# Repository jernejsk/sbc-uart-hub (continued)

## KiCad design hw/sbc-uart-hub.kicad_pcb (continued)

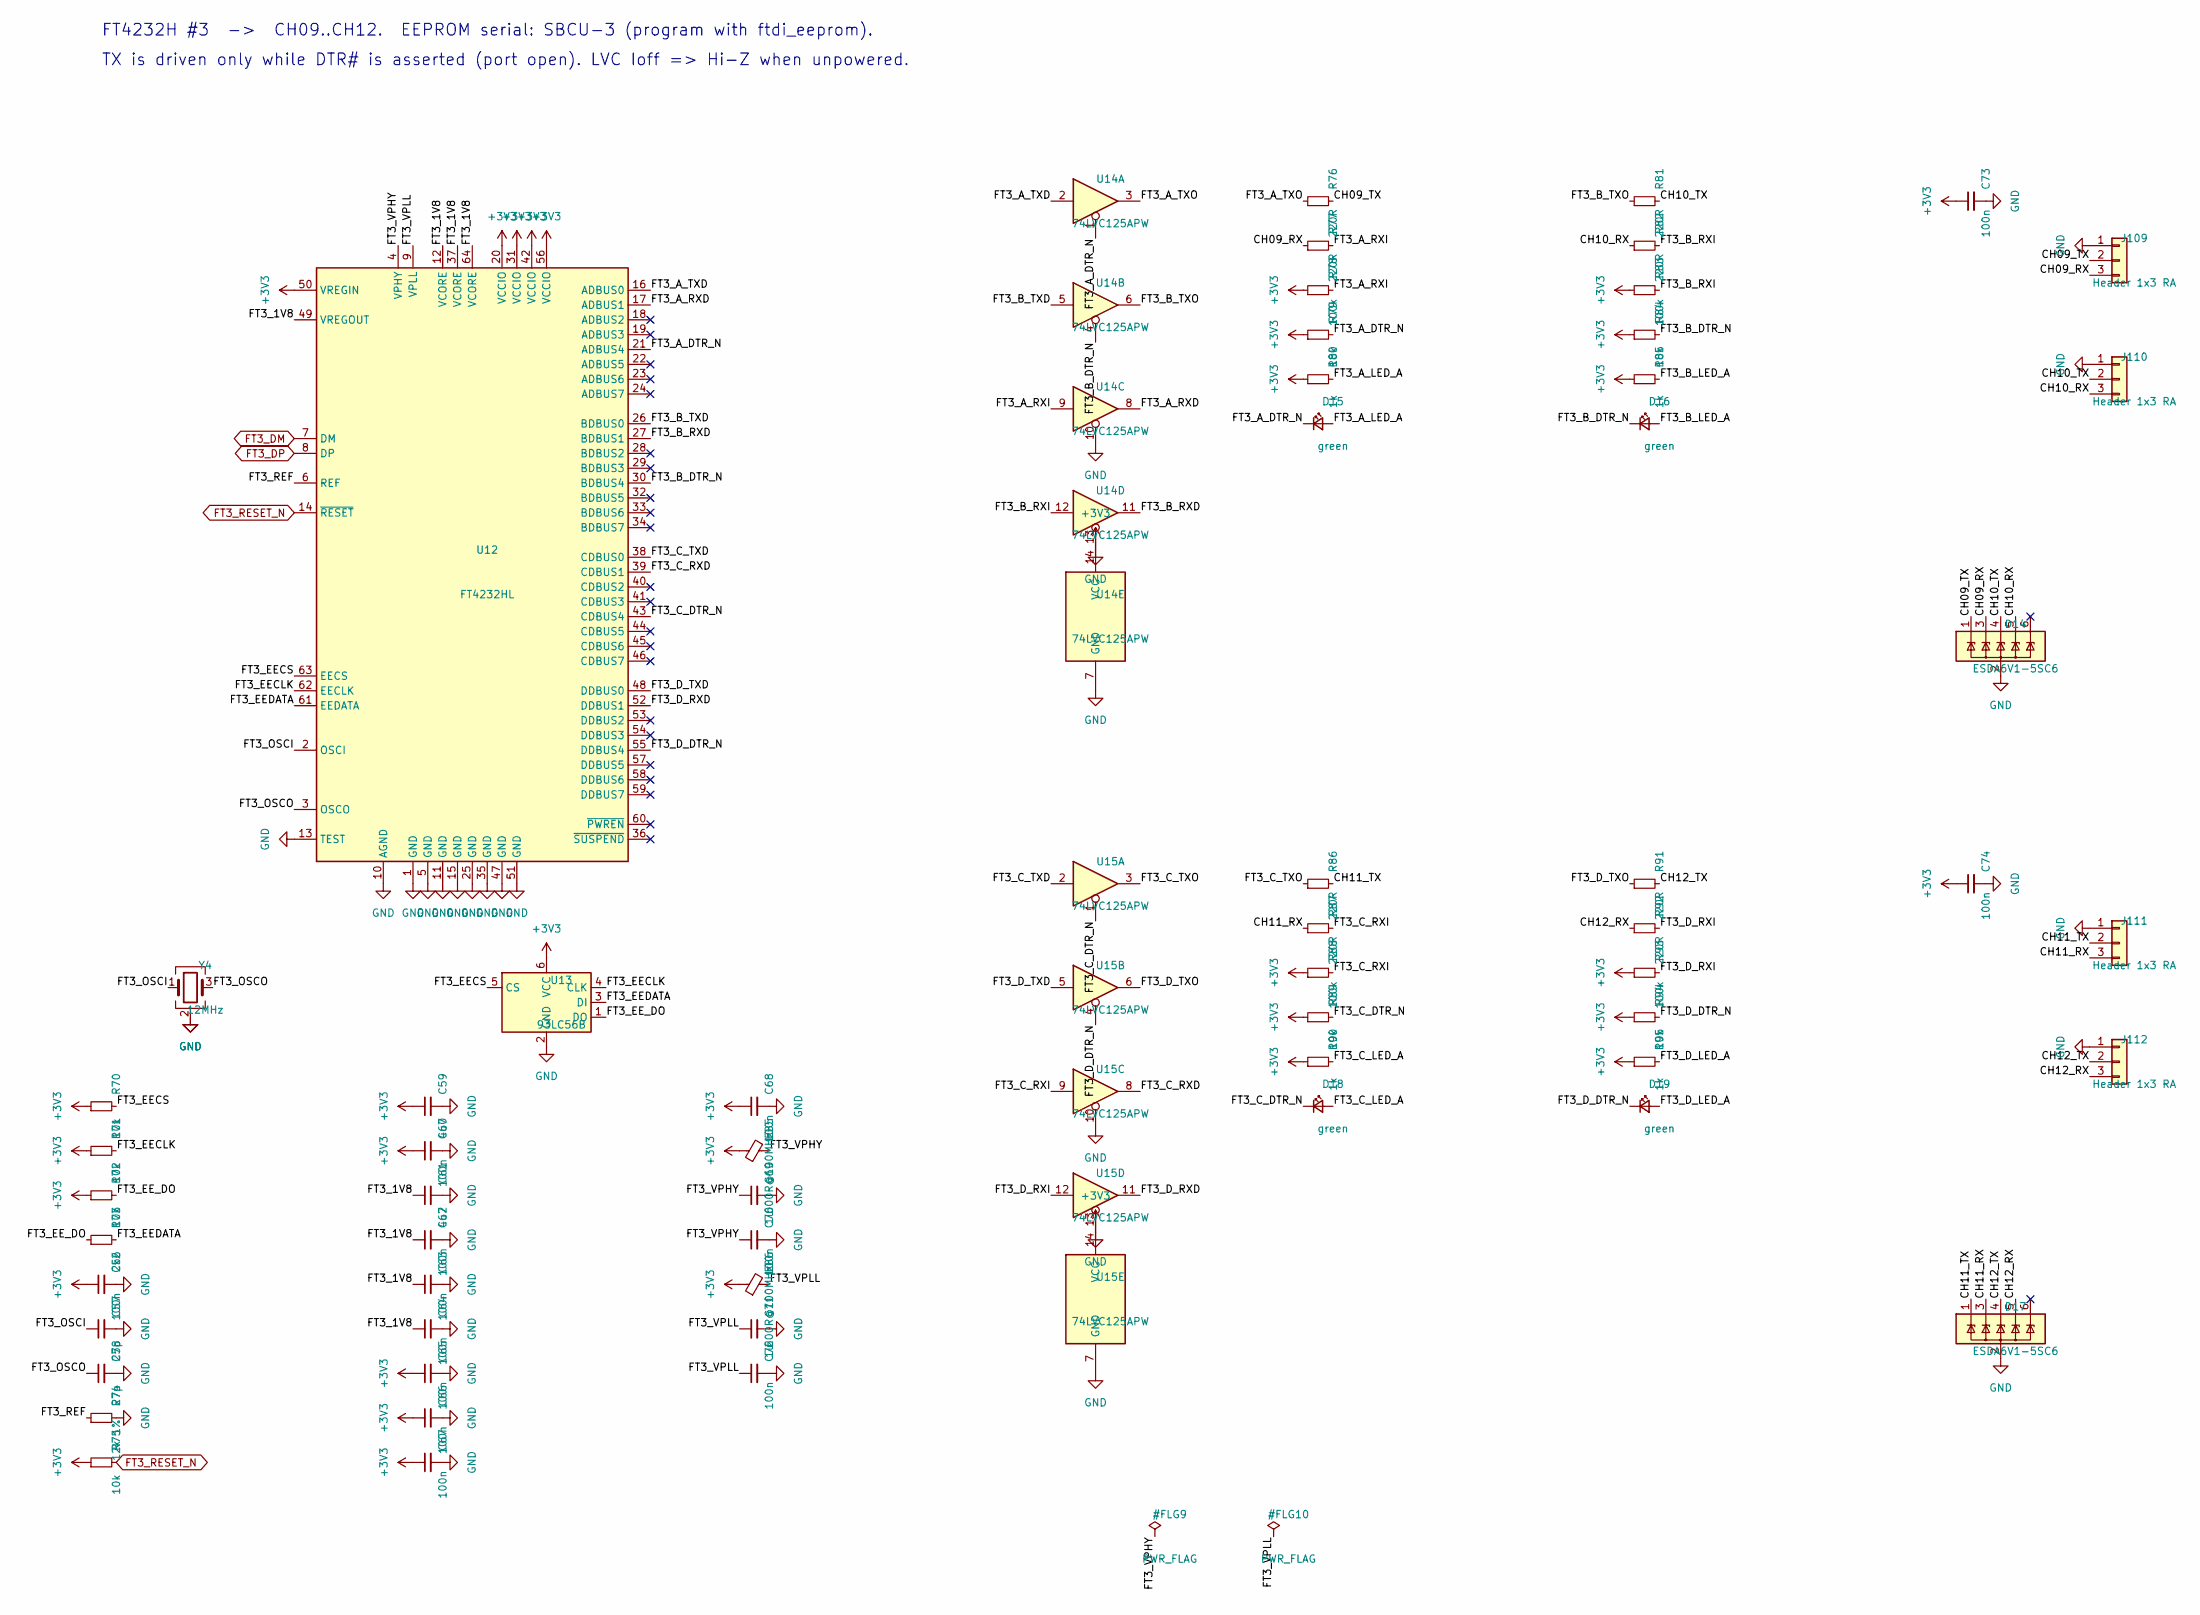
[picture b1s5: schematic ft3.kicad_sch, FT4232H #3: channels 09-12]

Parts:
C56, C60, C62, C63, C64, C65, C66, C67, C68, C70, C72, C73, C74: 100n; C_0402_1005Metric; MPN CL05B104KO5NNNC; LCSC C1525
C57, C58: 27p; C_0402_1005Metric; MPN 0402CG270J500NT; LCSC C1557
C59, C61: 4u7; C_0805_2012Metric; MPN CL21A475KAQNNNE; LCSC C1779
C69, C71: 1u; C_0402_1005Metric; MPN CL05A105KA5NQNC; LCSC C52923
D14, D17: ESDA6V1-5SC6; SOT-23-6; MPN ESDA6V1-5SC6; LCSC C2827672
D15, D16, D18, D19: green; LED_0603_1608Metric; MPN KT-0603G; LCSC C12624
FB5, FB6: 600R@100MHz; L_0603_1608Metric; MPN GZ1608D601TF; LCSC C1002
J109, J110, J111, J112: Header 1x3 RA; PinHeader_1x03_P2.54mm_Horizontal_Edge; MPN PZ254R-11-03P; LCSC C492411
R70, R71, R72, R75, R79, R84, R89, R94: 10k; R_0402_1005Metric; MPN 0402WGF1002TCE; LCSC C25744
R73: 2k2; R_0402_1005Metric; MPN 0402WGF2201TCE; LCSC C25879
R74: 12k 1%; R_0402_1005Metric; MPN 0402WGF1202TCE; LCSC C25752
R76, R77, R81, R82, R86, R87, R91, R92: 220R; R_0402_1005Metric; MPN 0402WGF2200TCE; LCSC C25091
R78, R83, R88, R93: 100k; R_0402_1005Metric; MPN 0402WGF1003TCE; LCSC C25741
R80, R85, R90, R95: 1k; R_0402_1005Metric; MPN 0402WGF1001TCE; LCSC C11702
U12: FT4232HL; LQFP-64_10x10mm_P0.5mm; MPN FT4232HL-REEL; LCSC C56742
U13: 93LC56B; SOT-23-6; MPN 93LC56BT-I/OT; LCSC C190271
U14, U15: 74LVC125APW; TSSOP-14_4.4x5mm_P0.65mm; MPN 74LVC125APW,118; LCSC C6059
Y4: 12MHz; Crystal_SMD_3225-4Pin_3.2x2.5mm; MPN X322512MSB4SI; LCSC C9002

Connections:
+3V3: C56.1, C59.1, C60.1, C65.1, C66.1, C67.1, C68.1, C73.1, C74.1, FB5.1, FB6.1, R70.1, R71.1, R72.1, R75.1, R78.1, R79.1, R80.1, R83.1, R84.1, R85.1, R88.1, R89.1, R90.1, R93.1, R94.1, R95.1, U12.20 (VCCIO), U12.31 (VCCIO), U12.42 (VCCIO), U12.50 (VREGIN), U12.56 (VCCIO), U13.6 (VCC), U14.14 (VCC), U15.14 (VCC); also elsewhere on the board
/FT3/CH09_RX: D14.3 (IO2), J109.3, R77.1
/FT3/CH09_TX: D14.1 (IO1), J109.2, R76.2
/FT3/CH10_RX: D14.5 (IO4), J110.3, R82.1
/FT3/CH10_TX: D14.4 (IO3), J110.2, R81.2
/FT3/CH11_RX: D17.3 (IO2), J111.3, R87.1
/FT3/CH11_TX: D17.1 (IO1), J111.2, R86.2
/FT3/CH12_RX: D17.5 (IO4), J112.3, R92.1
/FT3/CH12_TX: D17.4 (IO3), J112.2, R91.2
/FT3/FT3_1V8: C61.1, C62.1, C63.1, C64.1, U12.12 (VCORE), U12.37 (VCORE), U12.49 (VREGOUT), U12.64 (VCORE)
/FT3/FT3_A_DTR_N: D15.1 (K), R79.2, U12.21 (ADBUS4), U14.1
/FT3/FT3_A_LED_A: D15.2 (A), R80.2
/FT3/FT3_A_RXD: U12.17 (ADBUS1), U14.8
/FT3/FT3_A_RXI: R77.2, R78.2, U14.9
/FT3/FT3_A_TXD: U12.16 (ADBUS0), U14.2
/FT3/FT3_A_TXO: R76.1, U14.3
/FT3/FT3_B_DTR_N: D16.1 (K), R84.2, U12.30 (BDBUS4), U14.4
/FT3/FT3_B_LED_A: D16.2 (A), R85.2
/FT3/FT3_B_RXD: U12.27 (BDBUS1), U14.11
/FT3/FT3_B_RXI: R82.2, R83.2, U14.12
/FT3/FT3_B_TXD: U12.26 (BDBUS0), U14.5
/FT3/FT3_B_TXO: R81.1, U14.6
/FT3/FT3_C_DTR_N: D18.1 (K), R89.2, U12.43 (CDBUS4), U15.1
/FT3/FT3_C_LED_A: D18.2 (A), R90.2
/FT3/FT3_C_RXD: U12.39 (CDBUS1), U15.8
/FT3/FT3_C_RXI: R87.2, R88.2, U15.9
/FT3/FT3_C_TXD: U12.38 (CDBUS0), U15.2
/FT3/FT3_C_TXO: R86.1, U15.3
/FT3/FT3_D_DTR_N: D19.1 (K), R94.2, U12.55 (DDBUS4), U15.4
/FT3/FT3_D_LED_A: D19.2 (A), R95.2
/FT3/FT3_D_RXD: U12.52 (DDBUS1), U15.11
/FT3/FT3_D_RXI: R92.2, R93.2, U15.12
/FT3/FT3_D_TXD: U12.48 (DDBUS0), U15.5
/FT3/FT3_D_TXO: R91.1, U15.6
/FT3/FT3_EECLK: R71.2, U12.62 (EECLK), U13.4 (CLK)
/FT3/FT3_EECS: R70.2, U12.63 (EECS), U13.5 (CS)
/FT3/FT3_EEDATA: R73.2, U12.61 (EEDATA), U13.3 (DI)
/FT3/FT3_EE_DO: R72.2, R73.1, U13.1 (DO)
/FT3/FT3_OSCI: C57.1, U12.2 (OSCI), Y4.1
/FT3/FT3_OSCO: C58.1, U12.3 (OSCO), Y4.3
/FT3/FT3_REF: R74.1, U12.6 (REF)
/FT3/FT3_VPHY: C69.1, C70.1, FB5.2, U12.4 (VPHY)
/FT3/FT3_VPLL: C71.1, C72.1, FB6.2, U12.9 (VPLL)
FT3_DM: U12.7 (DM); also elsewhere on the board
FT3_DP: U12.8 (DP); also elsewhere on the board
FT3_RESET_N: R75.2, U12.14 (~RESET); also elsewhere on the board
GND: C56.2, C57.2, C58.2, C59.2, C60.2, C61.2, C62.2, C63.2, C64.2, C65.2, C66.2, C67.2, C68.2, C69.2, C70.2, C71.2, C72.2, C73.2, C74.2, D14.2 (GND), D17.2 (GND), J109.1, J110.1, J111.1, J112.1, R74.2, U12.1 (GND), U12.5 (GND), U12.10 (AGND), U12.11 (GND), U12.13 (TEST), U12.15 (GND), U12.25 (GND), U12.35 (GND), U12.47 (GND), U12.51 (GND), U13.2 (GND), U14.7 (GND), U14.10, U14.13, U15.7 (GND), U15.10, U15.13, Y4.2 (G), Y4.4 (G); also elsewhere on the board

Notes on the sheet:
FT4232H #3 -> CH09..CH12. EEPROM serial: SBCU-3 (program with ftdi_eeprom).
TX is driven only while DTR# is asserted (port open). LVC Ioff => Hi-Z when unpowered.

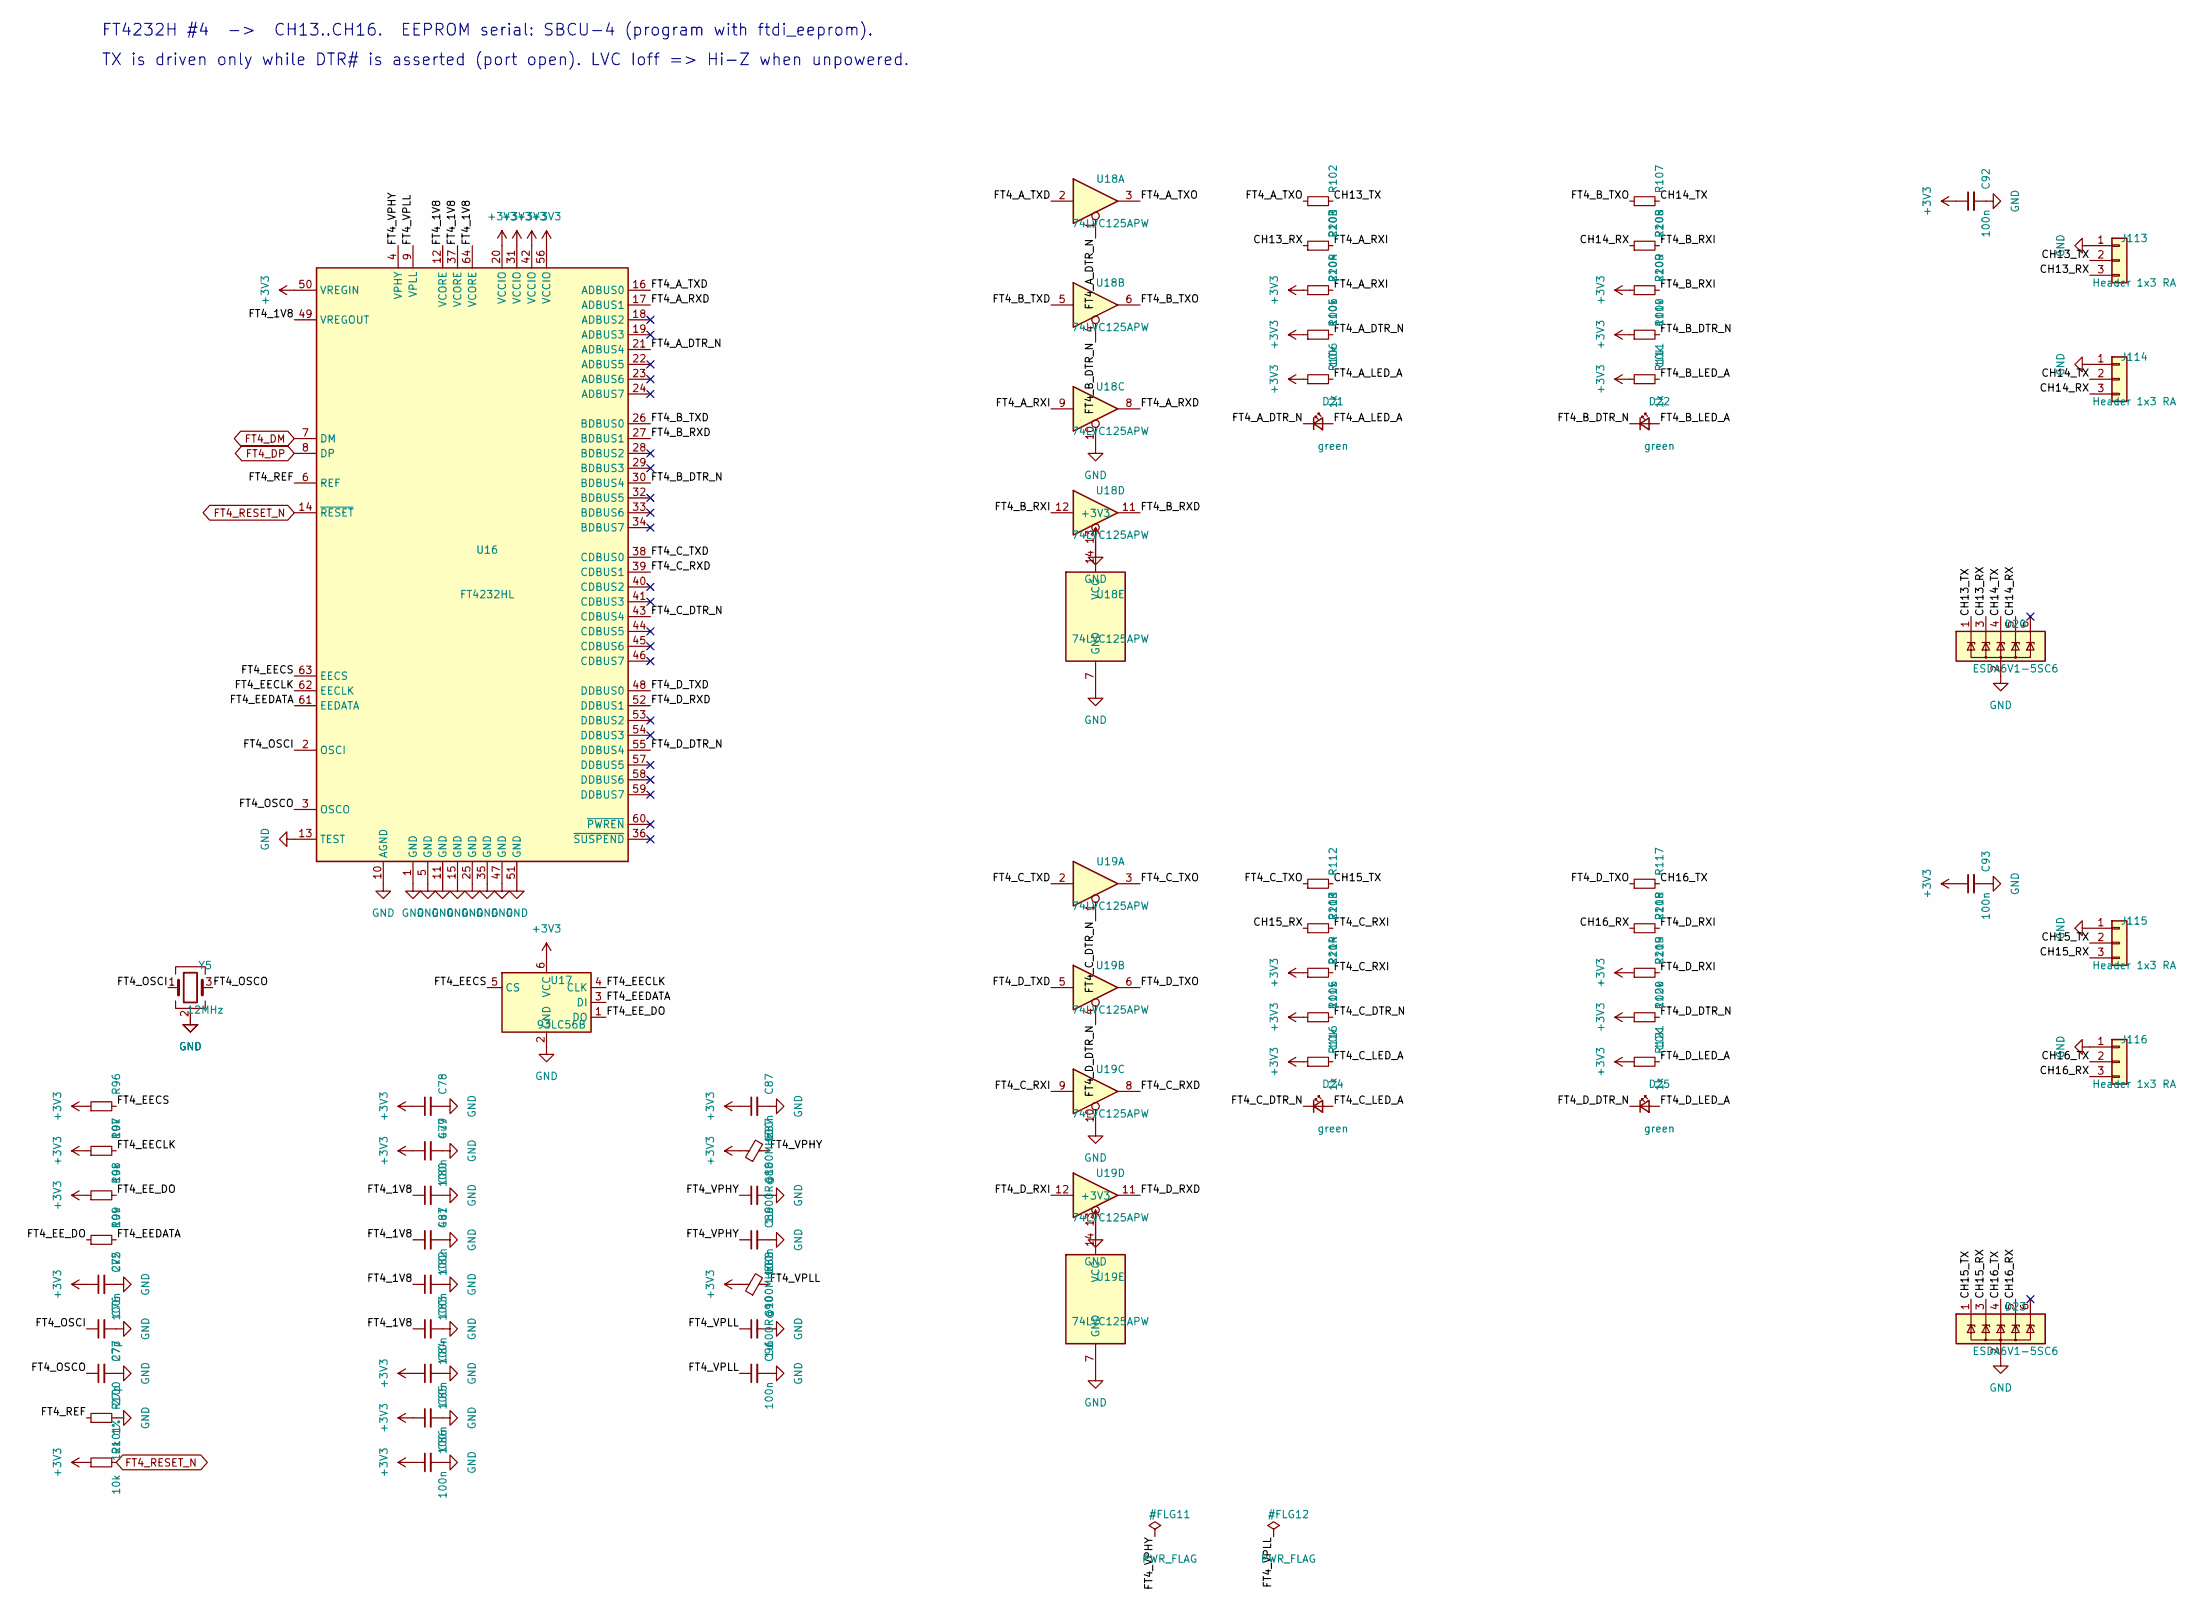
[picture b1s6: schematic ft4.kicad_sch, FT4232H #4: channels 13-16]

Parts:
C75, C79, C81, C82, C83, C84, C85, C86, C87, C89, C91, C92, C93: 100n; C_0402_1005Metric; MPN CL05B104KO5NNNC; LCSC C1525
C76, C77: 27p; C_0402_1005Metric; MPN 0402CG270J500NT; LCSC C1557
C78, C80: 4u7; C_0805_2012Metric; MPN CL21A475KAQNNNE; LCSC C1779
C88, C90: 1u; C_0402_1005Metric; MPN CL05A105KA5NQNC; LCSC C52923
D20, D23: ESDA6V1-5SC6; SOT-23-6; MPN ESDA6V1-5SC6; LCSC C2827672
D21, D22, D24, D25: green; LED_0603_1608Metric; MPN KT-0603G; LCSC C12624
FB7, FB8: 600R@100MHz; L_0603_1608Metric; MPN GZ1608D601TF; LCSC C1002
J113, J114, J115, J116: Header 1x3 RA; PinHeader_1x03_P2.54mm_Horizontal_Edge; MPN PZ254R-11-03P; LCSC C492411
R96, R97, R98, R101, R105, R110, R115, R120: 10k; R_0402_1005Metric; MPN 0402WGF1002TCE; LCSC C25744
R99: 2k2; R_0402_1005Metric; MPN 0402WGF2201TCE; LCSC C25879
R100: 12k 1%; R_0402_1005Metric; MPN 0402WGF1202TCE; LCSC C25752
R102, R103, R107, R108, R112, R113, R117, R118: 220R; R_0402_1005Metric; MPN 0402WGF2200TCE; LCSC C25091
R104, R109, R114, R119: 100k; R_0402_1005Metric; MPN 0402WGF1003TCE; LCSC C25741
R106, R111, R116, R121: 1k; R_0402_1005Metric; MPN 0402WGF1001TCE; LCSC C11702
U16: FT4232HL; LQFP-64_10x10mm_P0.5mm; MPN FT4232HL-REEL; LCSC C56742
U17: 93LC56B; SOT-23-6; MPN 93LC56BT-I/OT; LCSC C190271
U18, U19: 74LVC125APW; TSSOP-14_4.4x5mm_P0.65mm; MPN 74LVC125APW,118; LCSC C6059
Y5: 12MHz; Crystal_SMD_3225-4Pin_3.2x2.5mm; MPN X322512MSB4SI; LCSC C9002

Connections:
+3V3: C75.1, C78.1, C79.1, C84.1, C85.1, C86.1, C87.1, C92.1, C93.1, FB7.1, FB8.1, R96.1, R97.1, R98.1, R101.1, R104.1, R105.1, R106.1, R109.1, R110.1, R111.1, R114.1, R115.1, R116.1, R119.1, R120.1, R121.1, U16.20 (VCCIO), U16.31 (VCCIO), U16.42 (VCCIO), U16.50 (VREGIN), U16.56 (VCCIO), U17.6 (VCC), U18.14 (VCC), U19.14 (VCC); also elsewhere on the board
/FT4/CH13_RX: D20.3 (IO2), J113.3, R103.1
/FT4/CH13_TX: D20.1 (IO1), J113.2, R102.2
/FT4/CH14_RX: D20.5 (IO4), J114.3, R108.1
/FT4/CH14_TX: D20.4 (IO3), J114.2, R107.2
/FT4/CH15_RX: D23.3 (IO2), J115.3, R113.1
/FT4/CH15_TX: D23.1 (IO1), J115.2, R112.2
/FT4/CH16_RX: D23.5 (IO4), J116.3, R118.1
/FT4/CH16_TX: D23.4 (IO3), J116.2, R117.2
/FT4/FT4_1V8: C80.1, C81.1, C82.1, C83.1, U16.12 (VCORE), U16.37 (VCORE), U16.49 (VREGOUT), U16.64 (VCORE)
/FT4/FT4_A_DTR_N: D21.1 (K), R105.2, U16.21 (ADBUS4), U18.1
/FT4/FT4_A_LED_A: D21.2 (A), R106.2
/FT4/FT4_A_RXD: U16.17 (ADBUS1), U18.8
/FT4/FT4_A_RXI: R103.2, R104.2, U18.9
/FT4/FT4_A_TXD: U16.16 (ADBUS0), U18.2
/FT4/FT4_A_TXO: R102.1, U18.3
/FT4/FT4_B_DTR_N: D22.1 (K), R110.2, U16.30 (BDBUS4), U18.4
/FT4/FT4_B_LED_A: D22.2 (A), R111.2
/FT4/FT4_B_RXD: U16.27 (BDBUS1), U18.11
/FT4/FT4_B_RXI: R108.2, R109.2, U18.12
/FT4/FT4_B_TXD: U16.26 (BDBUS0), U18.5
/FT4/FT4_B_TXO: R107.1, U18.6
/FT4/FT4_C_DTR_N: D24.1 (K), R115.2, U16.43 (CDBUS4), U19.1
/FT4/FT4_C_LED_A: D24.2 (A), R116.2
/FT4/FT4_C_RXD: U16.39 (CDBUS1), U19.8
/FT4/FT4_C_RXI: R113.2, R114.2, U19.9
/FT4/FT4_C_TXD: U16.38 (CDBUS0), U19.2
/FT4/FT4_C_TXO: R112.1, U19.3
/FT4/FT4_D_DTR_N: D25.1 (K), R120.2, U16.55 (DDBUS4), U19.4
/FT4/FT4_D_LED_A: D25.2 (A), R121.2
/FT4/FT4_D_RXD: U16.52 (DDBUS1), U19.11
/FT4/FT4_D_RXI: R118.2, R119.2, U19.12
/FT4/FT4_D_TXD: U16.48 (DDBUS0), U19.5
/FT4/FT4_D_TXO: R117.1, U19.6
/FT4/FT4_EECLK: R97.2, U16.62 (EECLK), U17.4 (CLK)
/FT4/FT4_EECS: R96.2, U16.63 (EECS), U17.5 (CS)
/FT4/FT4_EEDATA: R99.2, U16.61 (EEDATA), U17.3 (DI)
/FT4/FT4_EE_DO: R98.2, R99.1, U17.1 (DO)
/FT4/FT4_OSCI: C76.1, U16.2 (OSCI), Y5.1
/FT4/FT4_OSCO: C77.1, U16.3 (OSCO), Y5.3
/FT4/FT4_REF: R100.1, U16.6 (REF)
/FT4/FT4_VPHY: C88.1, C89.1, FB7.2, U16.4 (VPHY)
/FT4/FT4_VPLL: C90.1, C91.1, FB8.2, U16.9 (VPLL)
FT4_DM: U16.7 (DM); also elsewhere on the board
FT4_DP: U16.8 (DP); also elsewhere on the board
FT4_RESET_N: R101.2, U16.14 (~RESET); also elsewhere on the board
GND: C75.2, C76.2, C77.2, C78.2, C79.2, C80.2, C81.2, C82.2, C83.2, C84.2, C85.2, C86.2, C87.2, C88.2, C89.2, C90.2, C91.2, C92.2, C93.2, D20.2 (GND), D23.2 (GND), J113.1, J114.1, J115.1, J116.1, R100.2, U16.1 (GND), U16.5 (GND), U16.10 (AGND), U16.11 (GND), U16.13 (TEST), U16.15 (GND), U16.25 (GND), U16.35 (GND), U16.47 (GND), U16.51 (GND), U17.2 (GND), U18.7 (GND), U18.10, U18.13, U19.7 (GND), U19.10, U19.13, Y5.2 (G), Y5.4 (G); also elsewhere on the board

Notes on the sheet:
FT4232H #4 -> CH13..CH16. EEPROM serial: SBCU-4 (program with ftdi_eeprom).
TX is driven only while DTR# is asserted (port open). LVC Ioff => Hi-Z when unpowered.

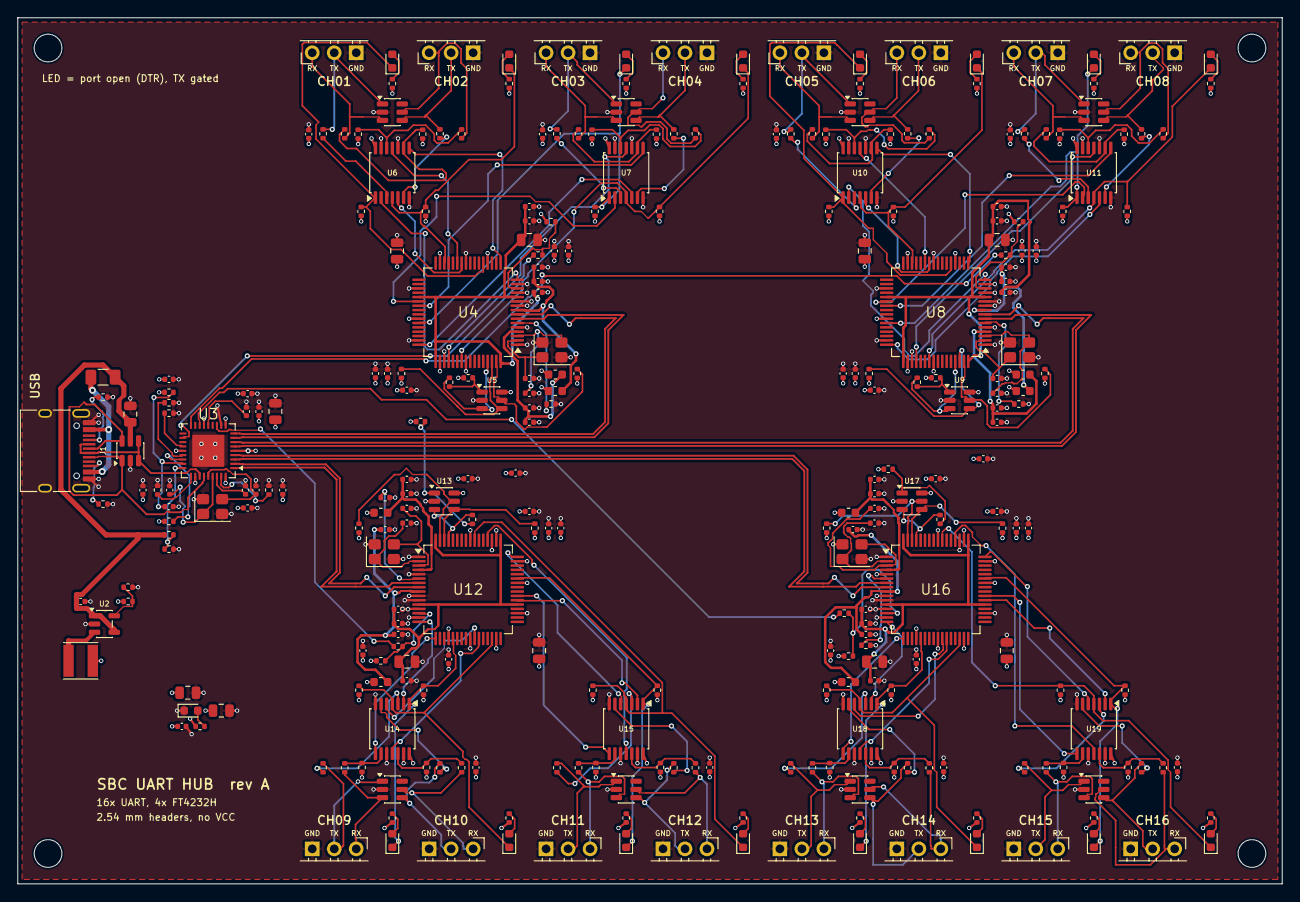
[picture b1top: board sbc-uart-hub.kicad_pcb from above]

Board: 4 copper layers, 146.0 x 100.0 mm, 294 parts (0 on the bottom side), 206 nets.

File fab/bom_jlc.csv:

Comment,Designator,Footprint,LCSC Part #,Qty
10u,"C1,C3,C4",C_0805_2012Metric,C15850,3
100n,"C2,C5,C6,C7,C8,C9,C10,C11,C13,C14,C18,C22,C24,C25,C26,C27,C28,C29,C30,C32,C34,C35,C36,C37,C41,C43,C44,C45,C46,C47,C48,C49,C51,C53,C54,C55,C56,C60,C62,C63,C64,C65,C66,C67,C68,C70,C72,C73,C74,C75,C79,C81,C82,C83,C84,C85,C86,C87,C89,C91,C92,C93",C_0402_1005Metric,C1525,62
4u7,"C12,C21,C23,C40,C42,C59,C61,C78,C80",C_0805_2012Metric,C1779,9
33p,"C15,C16",C_0402_1005Metric,C1562,2
1u,"C17,C31,C33,C50,C52,C69,C71,C88,C90",C_0402_1005Metric,C52923,9
27p,"C19,C20,C38,C39,C57,C58,C76,C77",C_0402_1005Metric,C1557,8
red,D1,LED_0603_1608Metric,C2286,1
ESDA6V1-5SC6,"D2,D5,D8,D11,D14,D17,D20,D23",SOT-23-6,C2827672,8
green,"D3,D4,D6,D7,D9,D10,D12,D13,D15,D16,D18,D19,D21,D22,D24,D25",LED_0603_1608Metric,C12624,16
1.1A,F1,Fuse_1206_3216Metric,C20801,1
600R@100MHz,"FB1,FB2,FB3,FB4,FB5,FB6,FB7,FB8",L_0603_1608Metric,C1002,8
USB-C,J1,USB_C_Receptacle_HRO_TYPE-C-31-M-12,C165948,1
Header 1x3 RA,"J101,J102,J103,J104,J105,J106,J107,J108,J109,J110,J111,J112,J113,J114,J115,J116",PinHeader_1x03_P2.54mm_Horizontal_Edge,C492411,16
2u2,L1,L_Taiyo-Yuden_NR-40xx,C83423,1
5k1,"R1,R2",R_0402_1005Metric,C25905,2
100k,"R3,R8,R9,R10,R11,R12,R13,R26,R31,R36,R41,R52,R57,R62,R67,R78,R83,R88,R93,R104,R109,R114,R119",R_0402_1005Metric,C25741,23
22k,R4,R_0402_1005Metric,C25768,1
1k,"R5,R28,R33,R38,R43,R54,R59,R64,R69,R80,R85,R90,R95,R106,R111,R116,R121",R_0402_1005Metric,C11702,17
12k 1%,"R6,R22,R48,R74,R100",R_0402_1005Metric,C25752,5
10k,"R7,R18,R19,R20,R23,R27,R32,R37,R42,R44,R45,R46,R49,R53,R58,R63,R68,R70,R71,R72,R75,R79,R84,R89,R94,R96,R97,R98,R101,R105,R110,R115,R120",R_0402_1005Metric,C25744,33
2k2,"R21,R47,R73,R99",R_0402_1005Metric,C25879,4
220R,"R24,R25,R29,R30,R34,R35,R39,R40,R50,R51,R55,R56,R60,R61,R65,R66,R76,R77,R81,R82,R86,R87,R91,R92,R102,R103,R107,R108,R112,R113,R117,R118",R_0402_1005Metric,C25091,32
USBLC6-2SC6,U1,SOT-23-6,C7519,1
TLV62569DBV,U2,SOT-23-5,C141836,1
USB2514B,U3,QFN-36-1EP_6x6mm_P0.5mm_EP3.7x3.7mm,C16251,1
FT4232HL,"U4,U8,U12,U16",LQFP-64_10x10mm_P0.5mm,C56742,4
93LC56B,"U5,U9,U13,U17",SOT-23-6,C190271,4
74LVC125APW,"U6,U7,U10,U11,U14,U15,U18,U19",TSSOP-14_4.4x5mm_P0.65mm,C6059,8
24MHz,Y1,Crystal_SMD_3225-4Pin_3.2x2.5mm,C15643,1
12MHz,"Y2,Y3,Y4,Y5",Crystal_SMD_3225-4Pin_3.2x2.5mm,C9002,4

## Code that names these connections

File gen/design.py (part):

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pw.text('USB-C (USB 2.0 only). Bus powered, budget ~0.45 A @5 V via buck.', (25.4, 22.86))
pw.place('Connector:USB_C_Receptacle_USB2.0_16P', 'J1', 'USB-C', (50.8, 76.2),
         fields=fields('C165948', 'TYPE-C-31-M-12'), fp='Connector_USB:USB_C_Receptacle_HRO_TYPE-C-31-M-12',
         pins={'A1': 'GND', 'A4': 'VBUS', 'A5': 'CC1', 'B5': 'CC2', 'A6': 'USB_UP_DP', 'B6': 'USB_UP_DP',
               'A7': 'USB_UP_DM', 'B7': 'USB_UP_DM', 'A8': None, 'B8': None, 'S1': 'GND'})
pw.place('Power_Protection:USBLC6-2SC6', d.next_ref('U'), 'USBLC6-2SC6', (127, 63.5),
         fields=fields('C7519', 'USBLC6-2SC6'), fp='Package_TO_SOT_SMD:SOT-23-6',
         pins={'1': 'USB_UP_DP', '6': 'USB_UP_DP', '3': 'USB_UP_DM', '4': 'USB_UP_DM', '2': 'GND', '5': '+5V'})
pw.place('Regulator_Switching:TLV62569DBV', d.next_ref('U'), 'TLV62569DBV', (127, 127),
         fields=fields('C141836', 'TLV62569DBVR'), fp='Package_TO_SOT_SMD:SOT-23-5',
         pins={'1': '+5V', '4': '+5V', '2': 'GND', '3': 'BUCK_SW', '5': 'BUCK_FB'})
t = Table(pw, 190.5, 50.8, rows=14)
t.add('R0402', '5k1', 'CC1', 'GND')
t.add('R0402', '5k1', 'CC2', 'GND')
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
